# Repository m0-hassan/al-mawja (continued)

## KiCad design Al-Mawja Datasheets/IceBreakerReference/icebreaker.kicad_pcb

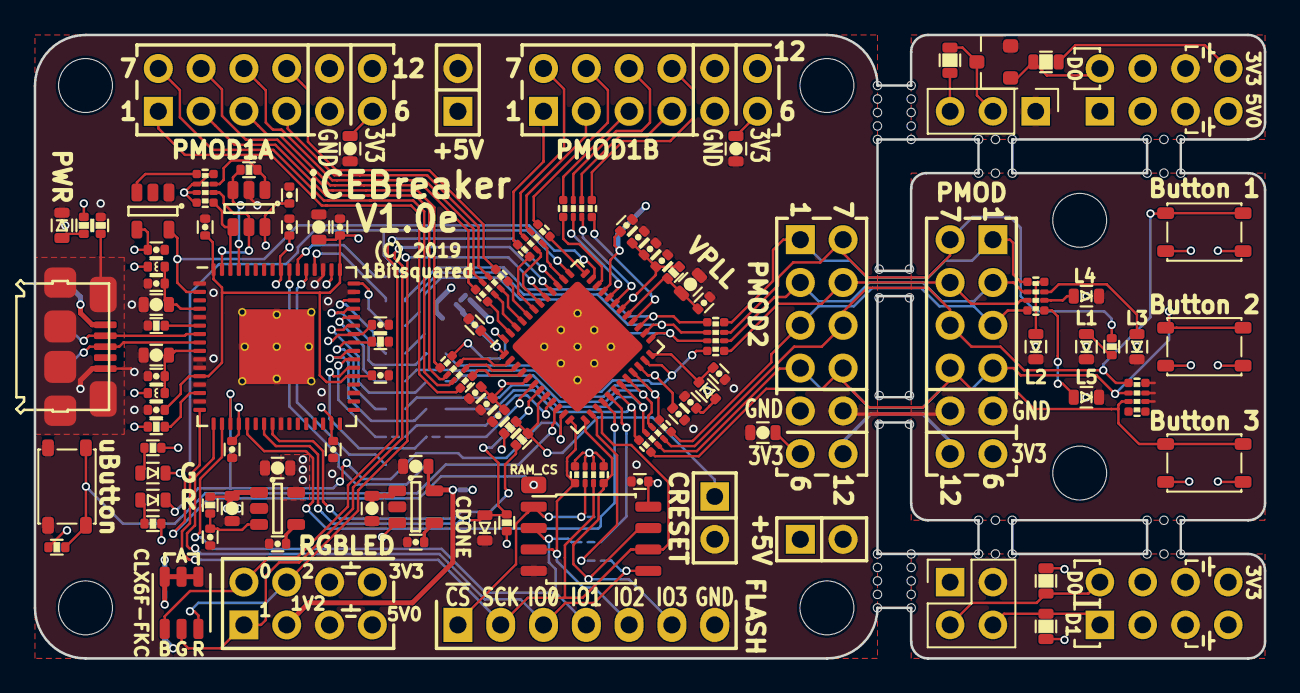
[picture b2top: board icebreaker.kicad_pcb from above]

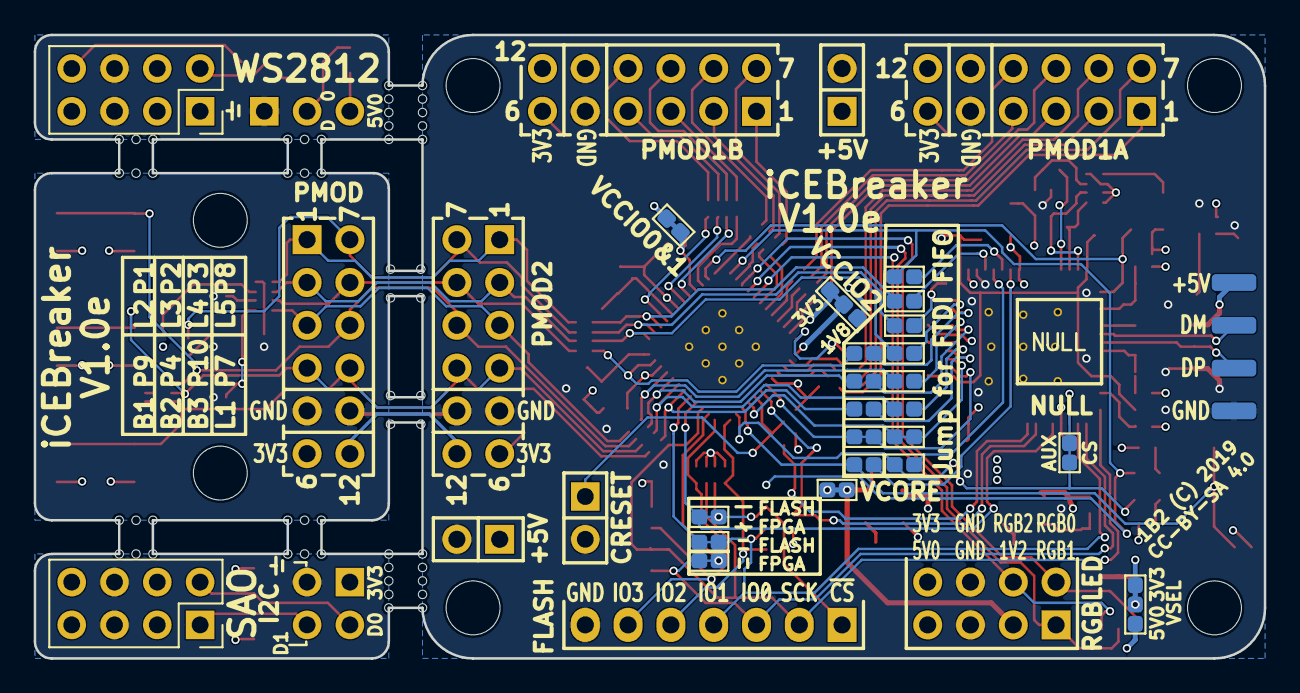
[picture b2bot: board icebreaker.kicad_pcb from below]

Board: 4 copper layers, 73.0 x 37.0 mm, 133 parts (27 on the bottom side), 126 nets.

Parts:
C1, C4, C10, C12, C13, C14, C16, C17, C18, C19, C20, C21, C22, C25, C26, C27, C29, C30, C31, C37: 100n; C_0402
C2, C5, C6, C7, C8, C9, C15: 4u7; C_0603
C3, C11, C28, C38: 10n; C_0402
C23, C36, C39: 1u; C_0402
C24: 10u; C_0603
C32, C33, C34: DNP; C_0603
C35: DNP; C_0402
D1, D4, D6, D7, D9, D10: GRN; D_0603
D2: ~800mVf; D_SOD-523
D3: BLU; D_0603
D5, D8: RED; D_0603
D11: LED_RGB; LED_Cree_PLCC6_3.4x3.4mm
J1, J2, J15, J16, J18, J29: Jumper; J_NC_0603_15
J3, J4, J5, J6, J7, J8, J9, J10, J11, J12, J13: Jumper; J_0603
J14, J19: Jumper; J_NC_0603_30
J17, J30: Jumper; J_NCNO_0903_30
J20: Flash; Pin_Header_Straight_1x07
J21, J22: PMOD; Socket_Strip_Angled_2x06
J23: PMOD; Socket_Strip_Straight_2x06
J24: PMOD; Pin_Header_Straight_2x06
J25: RGB Led; Pin_Header_Straight_2x04
J26, J27: 5V AUX; Pin_Header_Straight_2x01
J28: CRESET; PinHeader_2x01_P2.54mm_Vertical
J31, J33: RGB Led; PinSocket_2x04_P2.54mm_Vertical
J32: WS2812; PinHeader_1x03_P2.54mm_Vertical
J34: SADD; PinSocket_2x02_P2.54mm_Vertical
L1, L2: 600; L_0402
P1: pkl_USB_OTG; Connector_USB_Micro_B_SMD
P2, P3, P4, P5: UP; PAD_SMD_1x2.65
P6: RAM_CS; PAD_SMD_1x1.5
Q1: BSS138; SOT-23
R1: 1M; R_0402
R2, R11, R16: 10k; R_Array_Convex_4x0402
R3, R9, R13, R19, R25: 10k; R_0402
R4, R20, R21, R22, R23, R24: 33E; R_Array_Convex_4x0402
R5, R14, R15, R18: 330E; R_0402
R6, R12, R26: 2k2; R_0402
R7, R27, R28, R29: 10k; R_0603
R8: 12k; R_0402
R10: 100E; R_0402
R17: 330E; R_Array_Convex_4x0402
SW1, SW2, SW3, SW4: TACT; SW_SPST_3x4x2.5
U1: 93C46B-SOT-23-6; SOT-23-6
U2: 3.3V; SOT-23-5
U3: 1V2; SOT-23-5
U4: FT2232H; QFN-64-4.45mm1EP_9x9mm_Pitch0.5mm
U5: W25Q128JV-DTR; SOIC-8_5.3x5.3mm_Pitch1.27mm
U6: ICE40UP5K-SG48; QFN-48-1EP_7x7mm_Pitch0.5mm
U7: 12MHz; SOT-23-5

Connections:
+1V2: C15.1, J14.2, J25.3, U3.5
+1V8: C7.1, C10.1, C14.1, C16.1, C17.1, J17.3, U4.12, U4.37, U4.49, U4.64
+3V3: C1.1, C4.1, C5.1, C18.1, C19.1, C20.1, C21.1, C22.1, C29.1, C32.2, C33.2, C34.2, D2.A, J17.1, J19.2, J21.6, J21.12, J22.6, J22.12, J23.6, J23.12, J24.6, J24.12, J25.8, J30.1, L1.1, L2.1, R2.2, R2.4, R2.6, R2.7, R5.1, R9.2, R11.1, R11.3, R11.5, R11.7, R12.1, R13.2, R14.2, R15.2, R19.1, SW2.2, SW3.2, SW4.2, U1.6, U2.5, U4.20, U4.31, U4.42, U4.50, U4.56, U5.8, U7.4
+5V: C2.1, C8.1, J25.7, J26.1, J27.1, J30.3, P1.1, P2.1, R3.1, U2.1, U3.1, U3.3
/EB_3V3: J33.8, J34.1, R28.2, R29.2
/EB_GND: J33.5, J33.6, J34.3
/EB_OD0: J33.2, J34.2, R28.1
/EB_OD1: J33.1, J34.4, R29.1
/ET_3V3: J31.8, R7.1
/ET_5V: J31.7, J32.3, R27.1
/ET_GND: J31.5, J31.6, J32.1, Q1.2
/ET_O0: J32.2, Q1.3, R27.2
/ET_OD0: J31.2, Q1.1, R7.2
/FLASH_CS: J18.1, J20.1, R11.6, U5.1
/FLASH_MISO|IO1: J16.2, J20.4, U4.18, U5.2
/FLASH_MOSI|IO0: J15.1, J20.3, U4.17, U5.5
/FLASH_~HLD|~RST|IO3: J20.6, R11.2, U5.7, U6.13
/FLASH_~WP|IO2: J20.5, R11.8, U5.3, U6.12
/FTDI_CLK: U4.2, U6.35, U7.5
/P1A1: R20.1, U6.4
/P1A1x: J21.1, R20.2
/P1A2: R20.5, U6.2
/P1A2x: J21.2, R20.6
/P1A3: R23.1, U6.47
/P1A3x: J21.3, R23.2
/P1A4: R23.5, U6.45
/P1A4x: J21.4, R23.6
/P1A7: R20.3, U6.3
/P1A7x: J21.7, R20.4
/P1A8: R20.7, U6.48
/P1A8x: J21.8, R20.8
/P1A9: R23.3, U6.46
/P1A9x: J21.9, R23.4
/P1A10: R23.7, U6.44
/P1A10x: J21.10, R23.8
/P1B1: R21.1, U6.43
/P1B1x: J22.1, R21.2
/P1B2: R21.5, U6.38
/P1B2x: J22.2, R21.6
/P1B3: R24.1, U6.34
/P1B3x: J22.3, R24.2
/P1B4: R24.5, U6.31
/P1B4x: J22.4, R24.6
/P1B7: R21.3, U6.42
/P1B7x: J22.7, R21.4
/P1B8: R21.7, U6.36
/P1B8x: J22.8, R21.8
/P1B9: R24.3, U6.32
/P1B9x: J22.9, R24.4
/P1B10: R24.7, U6.28
/P1B10x: J22.10, R24.8
/P2_1: J10.2, R4.1, U6.27
/P2_1x: J23.1, J24.1, R4.2, R17.8
/P2_2: J8.2, R4.5, U6.25
/P2_2x: J23.2, J24.2, R4.6, R17.6
/P2_3: J6.2, R22.1, U6.21
/P2_3x: J23.3, J24.3, R17.2, R22.2
/P2_4: J4.2, R22.5, U6.19
/P2_4x: J23.4, J24.4, R16.3, R22.6, SW3.1
/P2_7: J9.2, R4.3, U6.26
/P2_7x: J23.7, J24.7, R4.4, R18.2
/P2_8: J7.2, R4.7, U6.23
/P2_8x: J23.8, J24.8, R4.8, R17.4
/P2_9: J5.2, R22.3, U6.20
/P2_9x: J23.9, J24.9, R16.1, R22.4, SW2.1
/P2_10: J3.2, R22.7, U6.18
/P2_10x: J23.10, J24.10, R16.5, R22.8, SW4.1
/Rx_TTL|FIFO_D0: J1.2, U6.6
/SPI_CS: J29.1, U4.19
/Tx_TTL|FIFO_D1: J2.2, U6.9
/USB_DM: P1.2, P3.1, U4.7
/USB_DP: P1.3, P4.1, U4.8
/VCCIO_0|1: C30.1, C31.1, J19.1, U6.22, U6.33
/VCCIO_2: C27.2, J17.2, U6.1
/VCCPLL: C24.1, C26.1, R10.1, U6.29
/VCORE: C23.1, C25.1, C28.1, C36.1, C37.1, C38.1, J14.1, R10.2, U6.5, U6.30
/VPP_2V5: C35.1, D2.C, U6.24
/iCE_CDONE: D3.A, R12.2, U4.23, U6.7
/iCE_CRESET: J28.1, R19.2, R26.1, U6.8
/iCE_SCK: J20.2, R11.4, U4.16, U5.6, U6.15
/iCE_SI: J16.1, U6.17
/iCE_SO: J15.2, U6.14
/iCE_SS_B: J18.2, U4.21, U6.16
/shield: P1.GND, R1.2
/xFIFO_D0: J1.1, U4.38
/xFIFO_D1: J2.1, U4.39
/xFIFO_D2: J3.1, U4.40
/xFIFO_D3: J4.1, R25.1, U4.41
/xFIFO_D4: J5.1, U4.43
/xFIFO_D5: J6.1, U4.44
/xFIFO_D6: J7.1, U4.45
/xFIFO_D7: J8.1, U4.46
/xFIFO_WKUP: J13.1, U4.55
/xFIFO_~RD: J11.1, U4.53
/xFIFO_~RXF: J9.1, U4.48
/xFIFO_~TXE: J10.1, U4.52
/xFIFO_~WR: J12.1, U4.54
/xiCE_CRESET: R26.2, U4.24
/~BUTTON: J13.2, R13.1, SW1.1, U6.10
/~LEDG: D4.C, J12.2, P6.1, U6.37
/~LEDR: D5.C, J11.2, J29.2, U6.11
/~LED_RGB0: D11.1, J25.2, U6.39
/~LED_RGB1: D11.2, J25.1, U6.40
/~LED_RGB2: D11.3, J25.4, U6.41
GND: C1.2, C2.2, C3.2, C4.2, C5.2, C6.2, C7.2, C8.2, C9.2, C10.2, C11.2, C12.2, C13.2, C14.2, C15.2, C16.2, C17.2, C18.2, C19.2, C20.2, C21.2, C22.2, C23.2, C24.2, C25.2, C26.2, C27.1, C28.2, C29.2, C30.2, C31.2, C32.1, C33.1, C34.1, C35.2, C36.2, C37.2, C38.2, C39.2, D1.C, D3.C, D6.C, D7.C, D8.C, D9.C, D10.C, J20.7, J21.5, J21.11, J22.5, J22.11, J23.5, J23.11, J24.5, J24.11, J25.5, J25.6, J26.2, J27.2, J28.2, P1.5, P5.1, R1.1, R8.2, R16.2, R16.4, R16.6, R25.2, SW1.2, U1.2, U2.2, U3.2, U4.1, U4.5, U4.10, U4.11, U4.13, U4.15, U4.25, U4.35, U4.47, U4.51, U4.65, U5.4, U6.49, U7.1
unnamed: C3.1, U2.4
unnamed: C11.1, U3.4
unnamed: C6.1, C12.1, L2.2, U4.4
unnamed: C9.1, C13.1, L1.2, U4.9
unnamed: C39.1, R3.2, U2.3
unnamed: D1.A, R5.2
unnamed: D4.A, R14.1
unnamed: D5.A, R15.1
unnamed: D6.A, R17.7
unnamed: D7.A, R17.3
unnamed: D8.A, R18.1
unnamed: D9.A, R17.1
unnamed: D10.A, R17.5
unnamed: D11.4, D11.5, D11.6, J30.2
unnamed: R2.1, U1.4, U4.62
unnamed: R2.3, U1.5, U4.63
unnamed: R2.5, R6.2, U1.1
unnamed: R2.8, U7.3
unnamed: R6.1, U1.3, U4.61
unnamed: R8.1, U4.6
unnamed: R9.1, U4.14
